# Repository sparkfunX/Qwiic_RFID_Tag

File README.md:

# SparkX ST25DV64KC Dynamic NFC/RFID Tag

<p align="center">
    
    <a href="https://twitter.com/intent/follow?screen_name=sparkfun">
                    </a>
</p>

<table class="table table-hover table-striped table-bordered">
    <tr align="center">
     <td></td>
    </tr>
    <tr align="center">
        <td><a href="https://www.sparkfun.com/products/19035">SparkFun Qwiic Dynamic RFID Tag - ST25DV64KC (SPX-19035)</a></td>
    </tr>
</table>

The STMicroelectronics ST25DV _**dynamic**_ Near Frequency Communication / Radio Frequency Identification tag ICs are awesome! The ST25DV64KC offers 64-kBit (8-kBytes) of EEPROM memory which can be accessed over both I2C and RF (NFC)! It's a state-of-the-art tag which conforms to ISO/IEC 15693 or NFC Forum Type 5 recommendations. You can read and write the tag's memory using NFC even while the tag is powered down or disconnected!

The EEPROM memory can be divided into four areas, each of which can have different levels of protection applied. Want to store your data so everyone has read and write access over both I2C and RF? You can do that.
In fact, that's the default! Want to store your data in an area which can only be read if you know the password, and cannot be written to (via RF)? You can do that too!

Our [Arduino Library](https://github.com/sparkfun/SparkFun_ST25DV64KC_Arduino_Library) provides all of the methods you need to read and write the user memory, control the read and write permissions, alter the area sizes and apply password control. Not only that! We've included extra methods which will let you read and write **NDEF (NFC Forum Data Exchange Format) URI, WiFi and Text records** which your smart phone can understand!

Do you want your project to be able to log up to 8-kBytes of data (via I2C) and then be able to read it using your smart phone - even if your project is powered off? Our library lets you do that!

Do you want to be able to write WiFi credentials (SSID and Password) into tag memory using your smart phone and then to be able to read them over I2C so your Arduino board can join the network? With our library you can do that too!

Do you want to be able to manufacture and test your product and then program it with keys or other credentials just before you ship? We've got you covered.

Are you developing equipment or appliances for the home? Would you like to store diagnostic information so that the repair engineer can access it using their smart phone? Our library lets you do that! Would you like the customer to be able to read the diagnostics with _their_ smart phone and then email them to you? Our library will let you do that too! (Apart from the email bit - obvs.. You will need to add that bit yourself.)

Are you designing a poster for your project? Do you want to be able to program your tag using Arduino and then stick it to your poster so people can interact with it? Hey, we've got you covered there too!

## Arduino Library Documentation

A full library use overview, API reference guide and key example walk-throughs are available on GitHub Pages - [sparkfun.github.io/SparkFun_ST25DV64KC_Arduino_Library](https://sparkfun.github.io/SparkFun_ST25DV64KC_Arduino_Library/)

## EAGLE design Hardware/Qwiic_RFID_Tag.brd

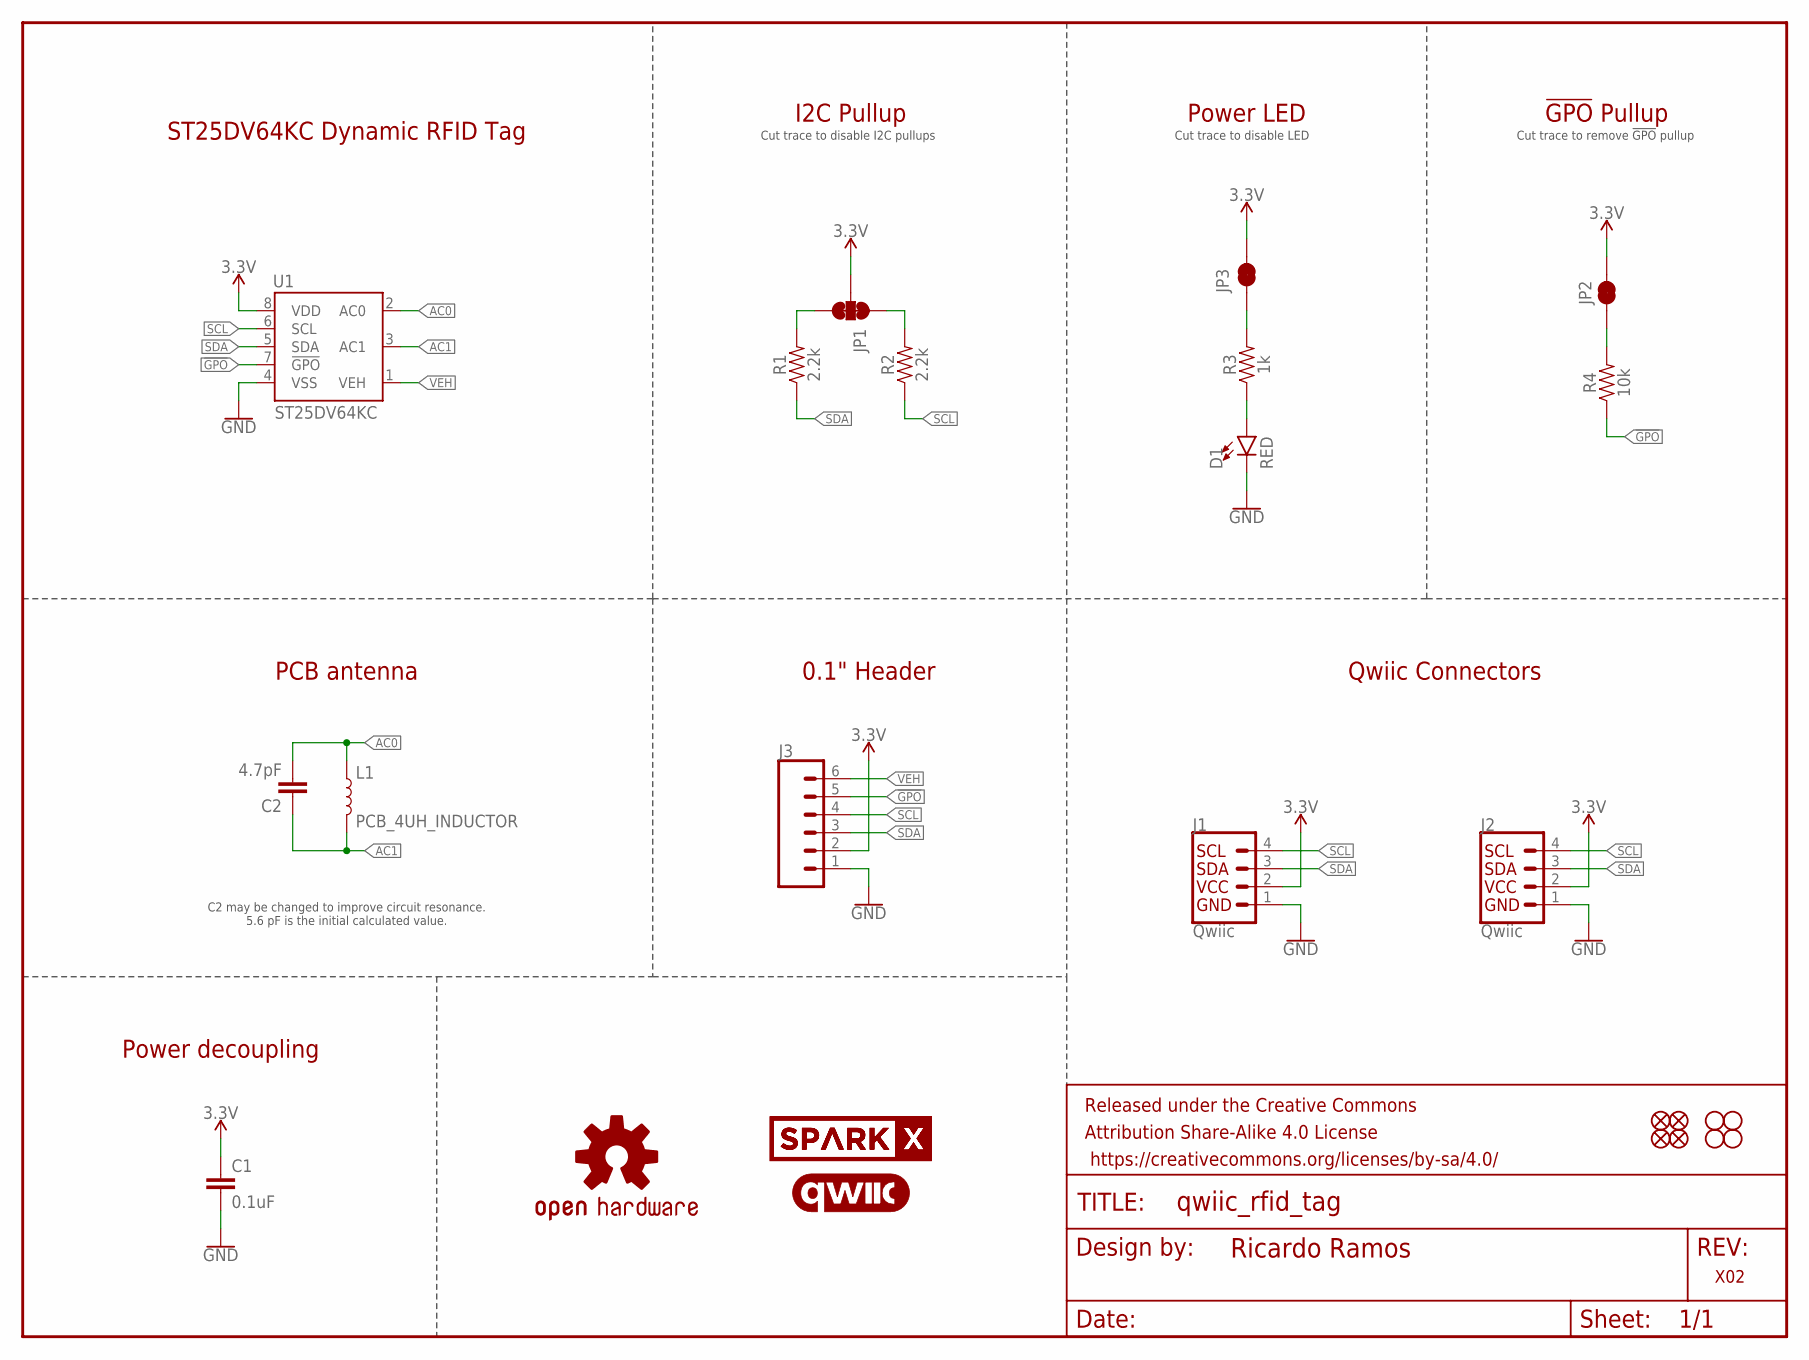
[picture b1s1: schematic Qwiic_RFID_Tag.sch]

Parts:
C1: 0.1uF; 0603
C2: 4.7pF; 0603
D1: RED; LED-0603
FD1, FD2, FD3, FD4: FIDUCIAL1X2; FIDUCIAL-1X2
FRAME1: FRAME-LETTERNO_PACKAGE; DUMMY
H1, H2, H3, H4: STAND-OFF
J1, J2: Qwiic; JST04_1MM_RA
J3: CONN_06NO_SILK_FEMALE_PTH; 1X06_NO_SILK
JP1: JUMPER-SMT_3_2-NC_TRACE_SILK; SMT-JUMPER_3_2-NC_TRACE_SILK
JP2, JP3: JUMPER-SMT_2_NC_TRACE_SILK; SMT-JUMPER_2_NC_TRACE_SILK
L1: PCB_4UH_INDUCTOR
LOGO1: OSHW-LOGOMINI; OSHW-LOGO-MINI
LOGO3: QWIIC_LOGO_7MM; QWIIC_7MM
R1, R2: 2.2k; 0603
R3: 1k; 0603
R4: 10k; 0603
U1: ST25DV64KC; SO08
U$1, U$2: SPARKX-LOGO5; SPARKX-LARGE

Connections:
3.3V: C1.1, J1.2, J2.2, J3.2, JP1.2, JP2.2, JP3.2, U1.8 (VDD)
!GPO!: J3.5, R4.1, U1.7 (!GPO!)
AC0: C2.2, L1.IN1 (1), U1.2 (AC0)
AC1: C2.1, L1.IN2 (2), U1.3 (AC1)
GND: C1.2, D1.C, J1.1, J2.1, J3.1, U1.4 (VSS)
unnamed: JP3.1, R3.2
unnamed: JP1.3, R1.2
unnamed: JP1.1, R2.2
unnamed: D1.A, R3.1
unnamed: JP2.1, R4.2
SCL: J1.4, J2.4, J3.4, R2.1, U1.6 (SCL)
SDA: J1.3, J2.3, J3.3, R1.1, U1.5 (SDA)
VEH: J3.6, U1.1 (VEH)

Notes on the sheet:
Qwiic Connectors
Cut trace to disable LED
Cut trace to remove !GPO! pullup
0.1" Header
PCB antenna
I2C Pullup
Power LED
!GPO! Pullup
ST25DV64KC Dynamic RFID Tag
Power decoupling
Cut trace to disable I2C pullups
C2 may be changed to improve circuit resonance. 5.6 pF is the initial calculated value.

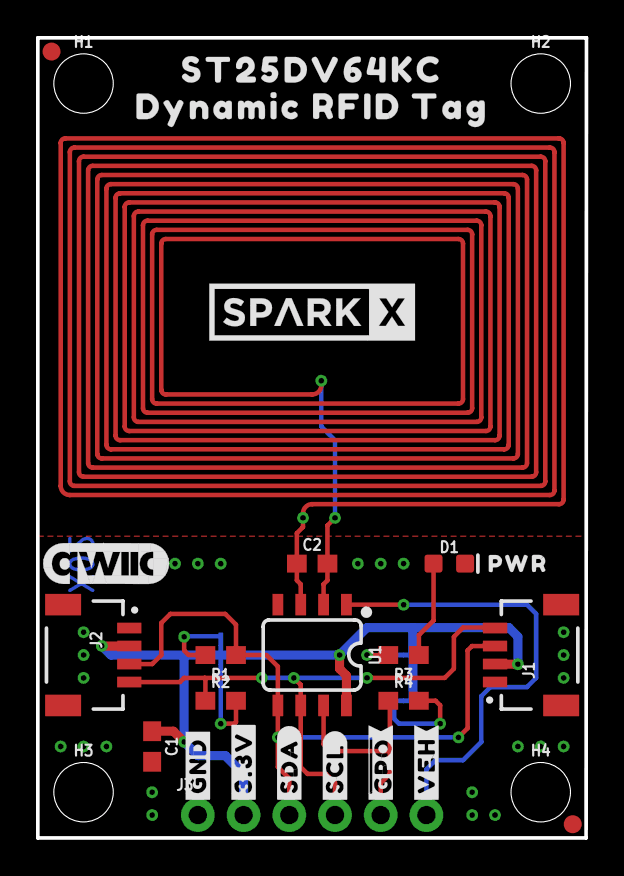
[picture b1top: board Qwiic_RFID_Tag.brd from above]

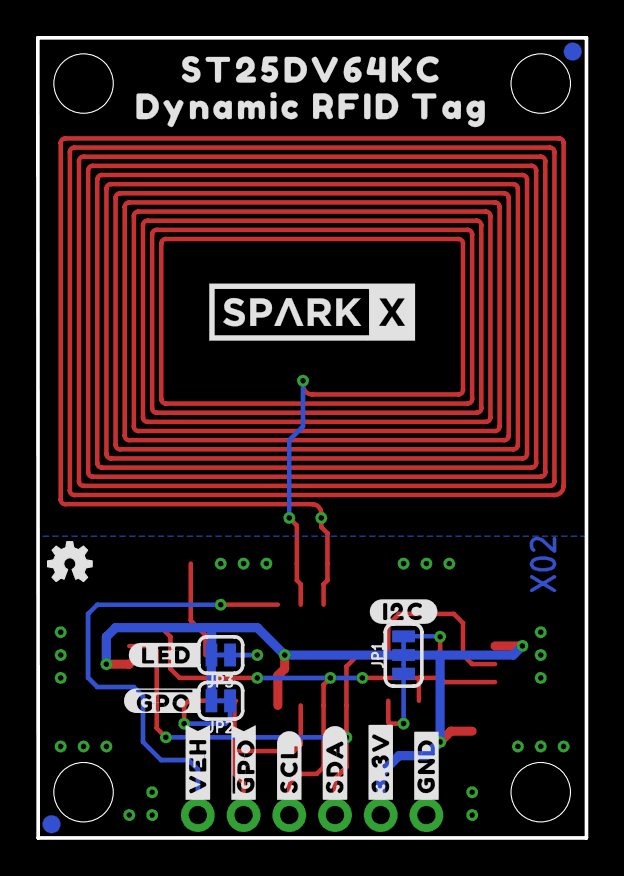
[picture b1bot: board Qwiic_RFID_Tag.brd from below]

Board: 2 copper layers, 30.5 x 44.5 mm, 48 parts (18 on the bottom side), 13 nets.

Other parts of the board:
U$3, U$19: #3#3V#0
U$4, U$18: #GND#4
U$5, U$20: #SDA#5
U$6, U$21: #SCL#6
U$7, U$22: ##GPO##8
U$8, U$23: #VEH#7
U$9: PWR11
U$10, U$11: DYNAMIC_RFID_TAG0
U$13, U$24: ST25DV64KC5984
U$15: #I2C#11
U$16: ##GPO##9
U$17: #LED#10

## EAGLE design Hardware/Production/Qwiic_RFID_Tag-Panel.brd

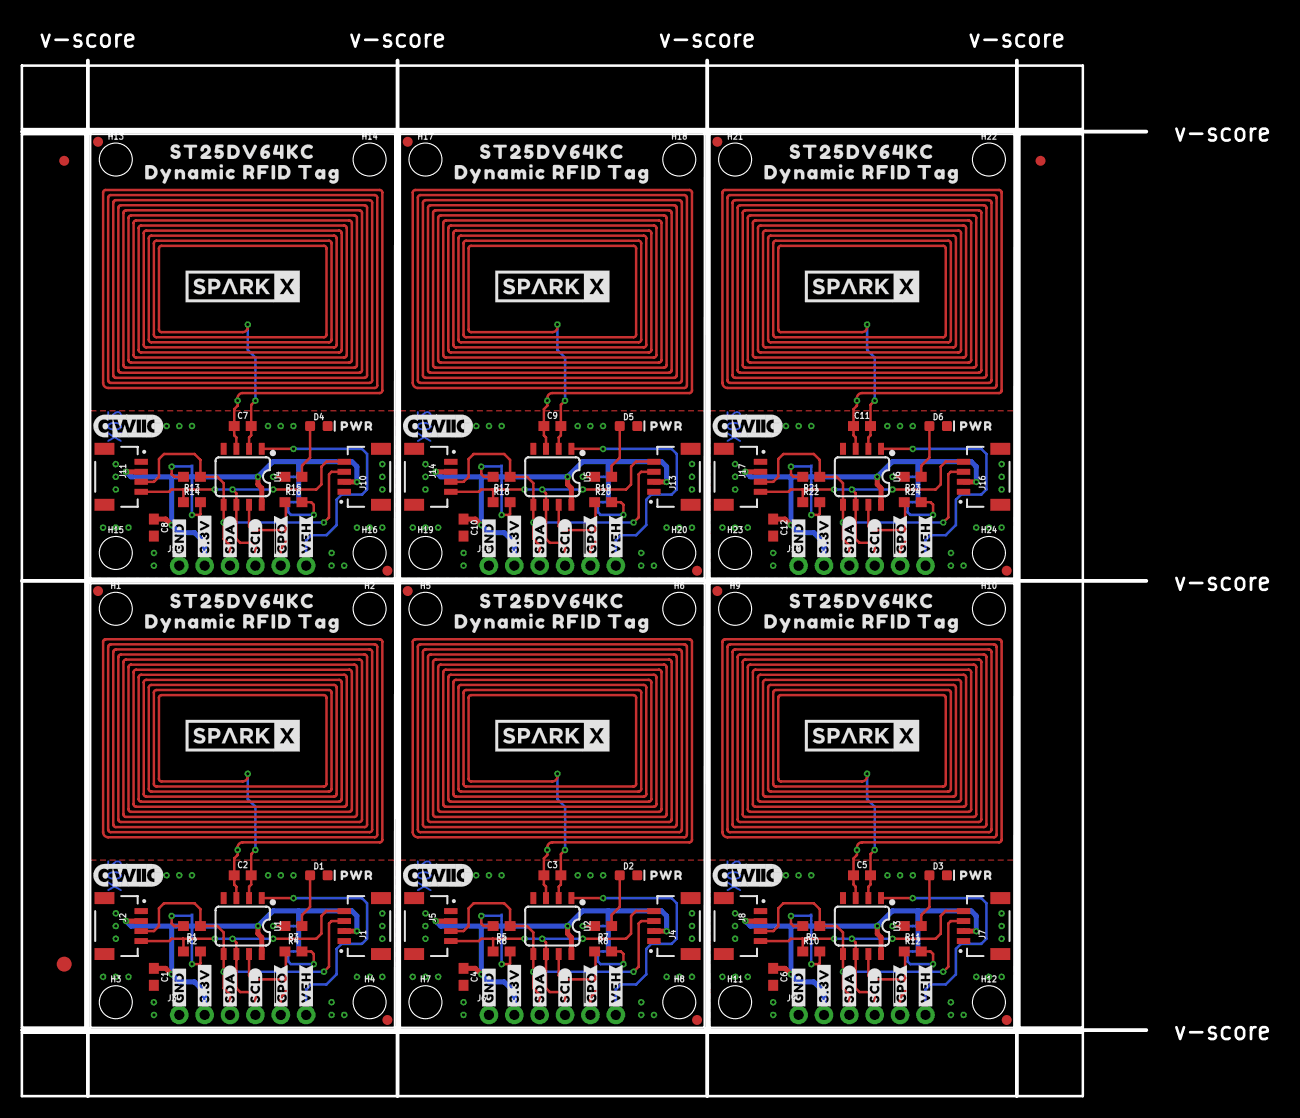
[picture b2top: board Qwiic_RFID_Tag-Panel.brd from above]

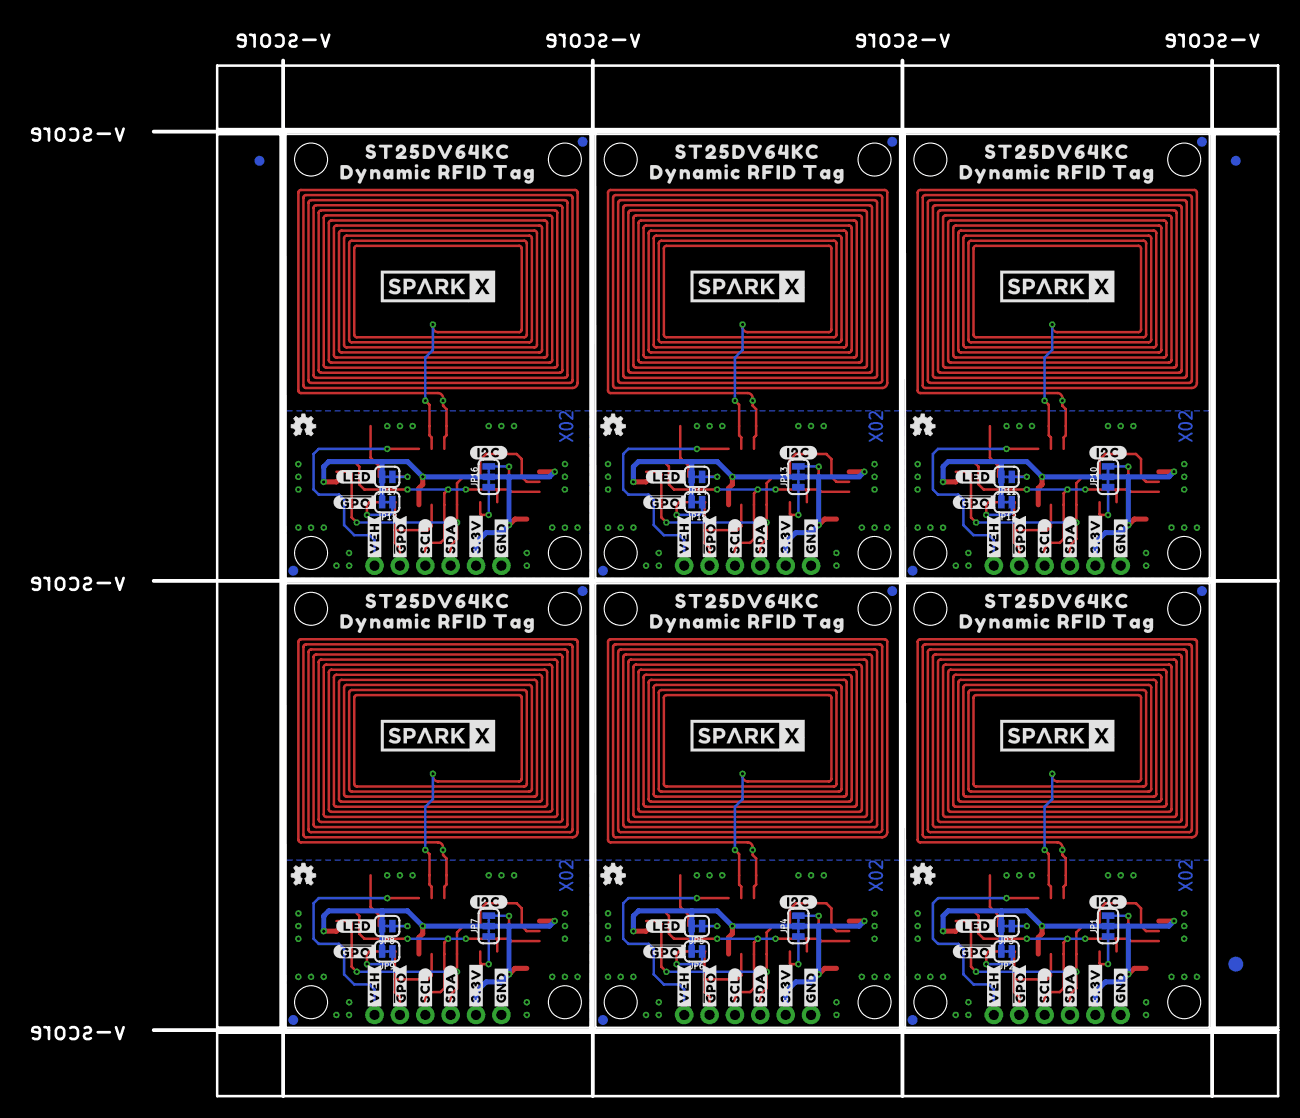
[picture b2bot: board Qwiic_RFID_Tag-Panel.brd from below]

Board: 2 copper layers, 112.5 x 103.6 mm, 294 parts (111 on the bottom side), 78 nets.

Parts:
C1, C4, C6, C8, C10, C12: 0.1uF; 0603
C2, C3, C5, C7, C9, C11: 4.7pF; 0603
D1, D2, D3, D4, D5, D6: RED; LED-0603
E$1, E$2, E$3, E$4: FIDUCIAL-1X2
E$5, E$6: FIDUCIAL-1.5X3
FD1, FD2, FD3, FD4, FD5, FD6, FD7, FD8, FD9, FD10, FD11, FD12, FD13, FD14, FD15, FD16, FD17, FD18, FD19, FD20, FD21, FD22, FD23, FD24: FIDUCIAL1X2; FIDUCIAL-1X2
FRAME1, FRAME2, FRAME3, FRAME4, FRAME5, FRAME6: FRAME-LETTERNO_PACKAGE; DUMMY
H1, H2, H3, H4, H5, H6, H7, H8, H9, H10, H11, H12, H13, H14, H15, H16, H17, H18, H19, H20, H21, H22, H23, H24: STAND-OFF
J1, J2, J4, J5, J7, J8, J10, J11, J13, J14, J16, J17: Qwiic; JST04_1MM_RA
J3, J6, J9, J12, J15, J18: 1X06_NO_SILK
JP1, JP4, JP7, JP10, JP13, JP16: JUMPER-SMT_3_2-NC_TRACE_SILK; SMT-JUMPER_3_2-NC_TRACE_SILK
JP2, JP3, JP5, JP6, JP8, JP9, JP11, JP12, JP14, JP15, JP17, JP18: JUMPER-SMT_2_NC_TRACE_SILK; SMT-JUMPER_2_NC_TRACE_SILK
L1, L2, L3, L4, L5, L6: PCB_4UH_INDUCTOR
LOGO1, LOGO2, LOGO5, LOGO7, LOGO9, LOGO11: OSHW-LOGOMINI; OSHW-LOGO-MINI
LOGO3, LOGO4, LOGO6, LOGO8, LOGO10, LOGO12: QWIIC_LOGO_7MM; QWIIC_7MM
R1, R2, R5, R6, R9, R10, R13, R14, R17, R18, R21, R22: 2.2k; 0603
R3, R7, R11, R15, R19, R23: 1k; 0603
R4, R8, R12, R16, R20, R24: 10k; 0603
U1, U2, U3, U4, U5, U6: ST25DV64KC; SO08
U$1, U$2, U$12, U$14, U$45, U$46, U$67, U$68, U$89, U$90, U$111, U$112: SPARKX-LOGO5; SPARKX-LARGE
U$3, U$19, U$25, U$36, U$47, U$58, U$69, U$80, U$91, U$102, U$113, U$124: #3#3V#0
U$4, U$18, U$26, U$35, U$48, U$57, U$70, U$79, U$92, U$101, U$114, U$123: #GND#4
U$5, U$20, U$27, U$37, U$49, U$59, U$71, U$81, U$93, U$103, U$115, U$125: #SDA#5
U$6, U$21, U$28, U$38, U$50, U$60, U$72, U$82, U$94, U$104, U$116, U$126: #SCL#6
U$7, U$22, U$29, U$39, U$51, U$61, U$73, U$83, U$95, U$105, U$117, U$127: ##GPO##8
U$8, U$23, U$30, U$40, U$52, U$62, U$74, U$84, U$96, U$106, U$118, U$128: #VEH#7
U$9, U$31, U$53, U$75, U$97, U$119: PWR11
U$10, U$11, U$43, U$44, U$65, U$66, U$87, U$88, U$109, U$110, U$131, U$132: DYNAMIC_RFID_TAG0
U$13, U$24, U$41, U$42, U$63, U$64, U$85, U$86, U$107, U$108, U$129, U$130: ST25DV64KC5984
U$15, U$32, U$54, U$76, U$98, U$120: #I2C#11
U$16, U$33, U$55, U$77, U$99, U$121: ##GPO##9
U$17, U$34, U$56, U$78, U$100, U$122: #LED#10

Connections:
3.3V: C1.1, J1.2, J2.2, J3.2, JP1.2, JP2.2, JP3.2, U1.8
3.3V1: C4.1, J4.2, J5.2, J6.2, JP4.2, JP5.2, JP6.2, U2.8
3.3V2: C6.1, J7.2, J8.2, J9.2, JP7.2, JP8.2, JP9.2, U3.8
3.3V3: C8.1, J10.2, J11.2, J12.2, JP10.2, JP11.2, JP12.2, U4.8
3.3V4: C10.1, J13.2, J14.2, J15.2, JP13.2, JP14.2, JP15.2, U5.8
3.3V5: C12.1, J16.2, J17.2, J18.2, JP16.2, JP17.2, JP18.2, U6.8
!GPO!: J3.5, R4.1, U1.7
!GPO!1: J6.5, R8.1, U2.7
!GPO!2: J9.5, R12.1, U3.7
!GPO!3: J12.5, R16.1, U4.7
!GPO!4: J15.5, R20.1, U5.7
!GPO!5: J18.5, R24.1, U6.7
AC0: C2.2, L1.IN1, U1.2
AC1: C2.1, L1.IN2, U1.3
AC2: C3.2, L2.IN1, U2.2
AC3: C3.1, L2.IN2, U2.3
AC4: C5.2, L3.IN1, U3.2
AC5: C5.1, L3.IN2, U3.3
AC6: C7.2, L4.IN1, U4.2
AC7: C7.1, L4.IN2, U4.3
AC8: C9.2, L5.IN1, U5.2
AC9: C9.1, L5.IN2, U5.3
AC10: C11.2, L6.IN1, U6.2
AC11: C11.1, L6.IN2, U6.3
GND: C1.2, D1.C, J1.1, J2.1, J3.1, U1.4
GND1: C4.2, D2.C, J4.1, J5.1, J6.1, U2.4
GND2: C6.2, D3.C, J7.1, J8.1, J9.1, U3.4
GND3: C8.2, D4.C, J10.1, J11.1, J12.1, U4.4
GND4: C10.2, D5.C, J13.1, J14.1, J15.1, U5.4
GND5: C12.2, D6.C, J16.1, J17.1, J18.1, U6.4
unnamed: JP3.1, R3.2
unnamed: JP1.3, R1.2
unnamed: JP1.1, R2.2
unnamed: D1.A, R3.1
unnamed: JP2.1, R4.2
unnamed: JP4.3, R5.2
unnamed: JP4.1, R6.2
unnamed: JP5.1, R7.2
unnamed: D2.A, R7.1
unnamed: JP6.1, R8.2
unnamed: JP7.3, R9.2
unnamed: JP7.1, R10.2
unnamed: JP8.1, R11.2
unnamed: D3.A, R11.1
unnamed: JP9.1, R12.2
unnamed: JP10.3, R13.2
unnamed: JP10.1, R14.2
unnamed: JP11.1, R15.2
unnamed: D4.A, R15.1
unnamed: JP12.1, R16.2
unnamed: JP13.3, R17.2
unnamed: JP13.1, R18.2
unnamed: JP14.1, R19.2
unnamed: D5.A, R19.1
unnamed: JP15.1, R20.2
unnamed: JP16.3, R21.2
unnamed: JP16.1, R22.2
unnamed: JP17.1, R23.2
unnamed: D6.A, R23.1
unnamed: JP18.1, R24.2
SCL: J1.4, J2.4, J3.4, R2.1, U1.6
SCL1: J4.4, J5.4, J6.4, R6.1, U2.6
SCL2: J7.4, J8.4, J9.4, R10.1, U3.6
SCL3: J10.4, J11.4, J12.4, R14.1, U4.6
SCL4: J13.4, J14.4, J15.4, R18.1, U5.6
SCL5: J16.4, J17.4, J18.4, R22.1, U6.6
SDA: J1.3, J2.3, J3.3, R1.1, U1.5
SDA1: J4.3, J5.3, J6.3, R5.1, U2.5
SDA2: J7.3, J8.3, J9.3, R9.1, U3.5
SDA3: J10.3, J11.3, J12.3, R13.1, U4.5
SDA4: J13.3, J14.3, J15.3, R17.1, U5.5
SDA5: J16.3, J17.3, J18.3, R21.1, U6.5
VEH: J3.6, U1.1
VEH1: J6.6, U2.1
VEH2: J9.6, U3.1
VEH3: J12.6, U4.1
VEH4: J15.6, U5.1
VEH5: J18.6, U6.1

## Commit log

2021-11-02 Initial version
2021-11-03 Fixed misaligned mounting hole; trimmed long schematic segment.
2021-11-03 Fixed wrong dimension callout.
2021-11-04 Fixed fiducial placement, board version size and polygon isolation.
2021-11-04 Created production files
2021-11-09 Created PCB production files.
2021-11-09 Renamed file to reflect version. Added PCB version to bottom silk.
2021-11-09 Added bom csv file.
2021-11-24 Added production files; updated BOM.
2022-08-14 Add schematic
2022-08-14 X02 PCB

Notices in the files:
README.md:
License: MIT
parts and their libraries:
SparkFun-Capacitors: Licensing: Creative Commons ShareAlike 4.0 International - https://creativecommons.org/licenses/by-sa/4.0
SparkFun-Aesthetics: Released under the Creative Commons Attribution Share-Alike 4.0 License
SparkFun-Aesthetics: https://creativecommons.org/licenses/by-sa/4.0
